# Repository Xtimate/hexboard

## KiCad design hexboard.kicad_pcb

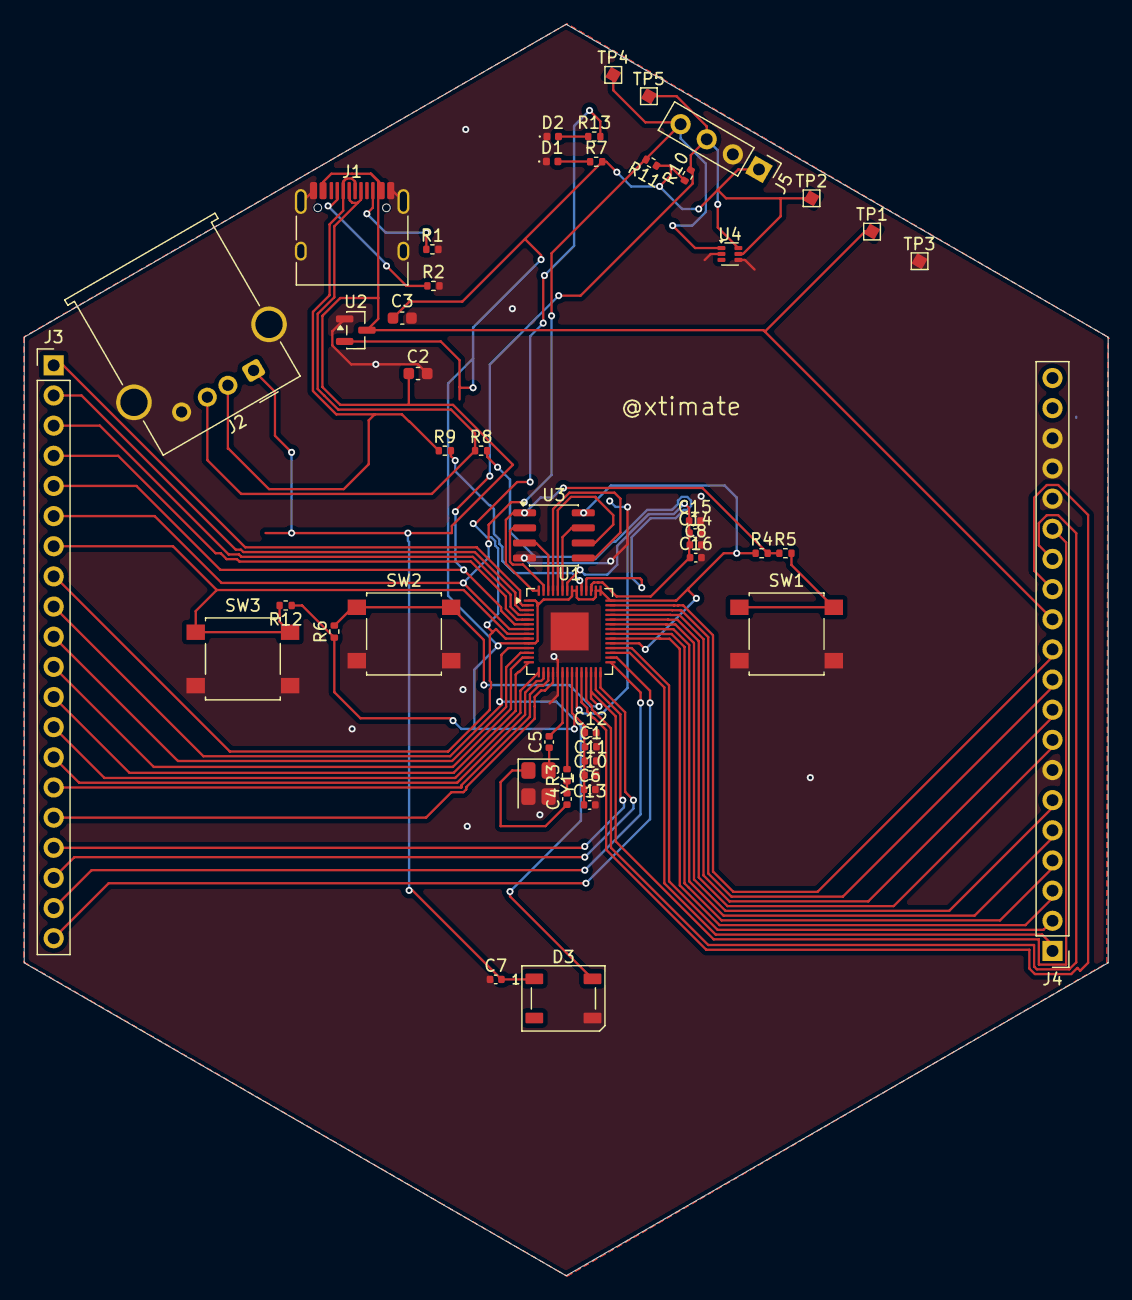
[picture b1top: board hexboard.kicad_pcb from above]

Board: 2 copper layers, 91.3 x 105.4 mm, 49 parts (0 on the bottom side), 55 nets.

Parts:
C1, C6, C7, C10, C11, C12, C13, C15, C16: 0.1uF; C_0402_1005Metric
C2, C3: 10uF; C_0603_1608Metric
C4, C5: 33pF; C_0402_1005Metric
C8, C14: 1uF; C_0402_1005Metric
D1, D2: LED; LED_0402_1005Metric
D3: WS2812B; LED_WS2812B_PLCC4_5.0x5.0mm_P3.2mm
J1: USB_C_Receptacle_USB2.0_16P; USB_C_Receptacle_HRO_TYPE-C-31-M-12
J2: USB_A; USB_A_Molex_67643_Horizontal
J3, J4: Conn_01x20; PinHeader_1x20_P2.54mm_Vertical
J5: Conn_01x04; PinHeader_1x04_P2.54mm_Vertical
R1, R2: 5.1K; R_0402_1005Metric
R3, R5: 1K; R_0402_1005Metric
R4, R6, R12: 10K; R_0402_1005Metric
R7, R13: 100 ohm; R_0402_1005Metric
R8, R9: 27 ohm; R_0402_1005Metric
R10, R11: 4.7K; R_0402_1005Metric
SW1, SW2, SW3: SW_Push; SW_SPST_B3S-1000
TP1: TESTVBUS; TestPoint_Pad_1.0x1.0mm
TP2: TEST_3V3; TestPoint_Pad_1.0x1.0mm
TP3: TESTGND; TestPoint_Pad_1.0x1.0mm
TP4: TESTSCL; TestPoint_Pad_1.0x1.0mm
TP5: TESTSDA; TestPoint_Pad_1.0x1.0mm
U1: RP2040; QFN-56-1EP_7x7mm_P0.4mm_EP3.2x3.2mm
U2: MCP1700x-330xxTT; SOT-23
U3: W25Q16JVSS; SOIC-8_3.9x4.9mm_P1.27mm
U4: TMP102xxDRL; SOT-563
Y1: Crystal_GND23_Small; Crystal_SMD_3225-4Pin_3.2x2.5mm

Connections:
+1V1: C8.1, C14.1, C15.1, C16.1, U1.23 (DVDD), U1.45 (VREG_VOUT), U1.50 (DVDD)
+3V3: C1.1, C3.1, C6.1, C10.1, C11.1, C12.1, C13.1, J5.1, R4.1, R6.1, R7.2, R10.1, R11.1, R12.1, TP2.1 (1_1), U1.1 (IOVDD), U1.10 (IOVDD), U1.22 (IOVDD), U1.33 (IOVDD), U1.42 (IOVDD), U1.43 (ADC_AVDD), U1.44 (VREG_VIN), U1.48 (USB_VDD), U1.49 (IOVDD), U2.2 (VO), U3.8 (VCC), U4.5 (V+)
/RUN: J4.15, R6.2, SW2.1, U1.26 (RUN)
/SWCLK: J4.13, U1.24 (SWCLK)
/SWDIO: J4.14, U1.25 (SWDIO)
GND: C1.2, C2.2, C3.2, C6.2, C7.1, C8.2, C10.2, C11.2, C12.2, C13.2, C14.2, C15.2, C16.2, D1.1 (K), D2.1 (K), D3.3 (VSS), J1.A1 (GND), J1.A12 (GND), J1.B1 (GND), J1.B12 (GND), J1.SH (SHIELD), J2.4 (GND), J2.SH (Shield), J4.7, J4.16, J4.17, J4.18, J5.2, R1.2, R2.2, SW1.2, SW2.2, SW3.2, TP3.1 (1_1), U1.19 (TESTEN), U1.57 (GND), U2.1 (GND), U3.4 (GND), U4.2 (GND), U4.4 (ADD0), Y1.2 (G), Y1.3 (G)
I2C_SCL: J3.6, J5.4, R11.2, TP4.1 (1_1), U1.7 (GPIO5), U4.1 (SCL)
I2C_SDA: J3.5, J5.3, R10.2, TP5.1 (1_1), U1.6 (GPIO4), U4.6 (SDA)
unnamed: C4.1, Y1.1
unnamed: D1.2 (A), R7.1
unnamed: D2.2 (A), R13.1
unnamed: J1.A5 (CC1), R2.1
unnamed: J1.B5 (CC2), R1.1
unnamed: J3.1, U1.2 (GPIO0)
unnamed: J3.2, U1.3 (GPIO1)
unnamed: J3.3, U1.4 (GPIO2)
unnamed: J3.4, U1.5 (GPIO3)
unnamed: J3.10, U1.12 (GPIO9)
unnamed: J3.11, U1.13 (GPIO10)
unnamed: J3.12, U1.14 (GPIO11)
unnamed: J3.13, U1.15 (GPIO12)
unnamed: J3.14, U1.16 (GPIO13)
unnamed: J3.15, U1.17 (GPIO14)
unnamed: J3.16, U1.18 (GPIO15)
unnamed: J3.17, U1.27 (GPIO16)
unnamed: J3.18, U1.28 (GPIO17)
unnamed: J3.19, U1.29 (GPIO18)
unnamed: J3.20, U1.30 (GPIO19)
unnamed: J4.1, U1.31 (GPIO20)
unnamed: J4.2, U1.32 (GPIO21)
unnamed: J4.3, U1.34 (GPIO22)
unnamed: J4.4, U1.35 (GPIO23)
unnamed: J4.5, U1.36 (GPIO24)
unnamed: J4.6, U1.37 (GPIO25)
unnamed: J4.8, U1.38 (GPIO26/ADC0)
unnamed: J4.9, U1.39 (GPIO27/ADC1)
unnamed: J4.10, U1.40 (GPIO28/ADC2)
unnamed: J4.11, U1.41 (GPIO29/ADC3)
unnamed: R5.2, SW1.1
QSPI_SCLK: U1.52 (QSPI_SCLK), U3.6 (CLK)
QSPI_SD0: U1.53 (QSPI_SD0), U3.5 (DI/IO_{0})
QSPI_SD1: U1.55 (QSPI_SD1), U3.2 (DO/IO_{1})
QSPI_SD2: U1.54 (QSPI_SD2), U3.3 (~WP/IO_{2})
QSPI_SD3: U1.51 (QSPI_SD3), U3.7 (~HOLD/~RESET/IO_{3})
QSPI_SS: R4.2, R5.1, U1.56 (~QSPI_SS), U3.1 (~CS)
RGB_DIN: D3.4 (DIN), J3.9, U1.11 (GPIO8)
USB_DM: J1.A7 (D-), J1.B7 (D-), J2.2 (D-), R9.1
USB_DM_MCU: R9.2, U1.47 (USB_DP)
USB_DP: J1.A6 (D+), J1.B6 (D+), J2.3 (D+), R8.1
USB_DP_MCU: R8.2, U1.46 (USB_DM)
USR_BTN: J3.7, R12.2, SW3.1, U1.8 (GPIO6)
USR_LED: J3.8, R13.2, U1.9 (GPIO7)
VBUS: C2.1, C7.2, D3.1 (VDD), J1.A4 (VBUS), J1.A9 (VBUS), J1.B4 (VBUS), J1.B9 (VBUS), J2.1 (VBUS), J4.12, TP1.1 (1_1), U2.3 (VI)
XIN: C5.1, C5.2, U1.20 (XIN), Y1.4
XOUT: C4.2, R3.1, R3.2, U1.21 (XOUT)

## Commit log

2026-05-12 initial schematic and pcb layout WIP
2026-05-12 recommit
2026-05-12 started routing headers
2026-05-12 added more header power lines
2026-05-12 more power lines
2026-05-12 more routing
2026-05-12 finished routing
2026-05-12 added hexagon design and handle on the front and started adding an oled header
2026-05-13 added design on back and added a few more things
